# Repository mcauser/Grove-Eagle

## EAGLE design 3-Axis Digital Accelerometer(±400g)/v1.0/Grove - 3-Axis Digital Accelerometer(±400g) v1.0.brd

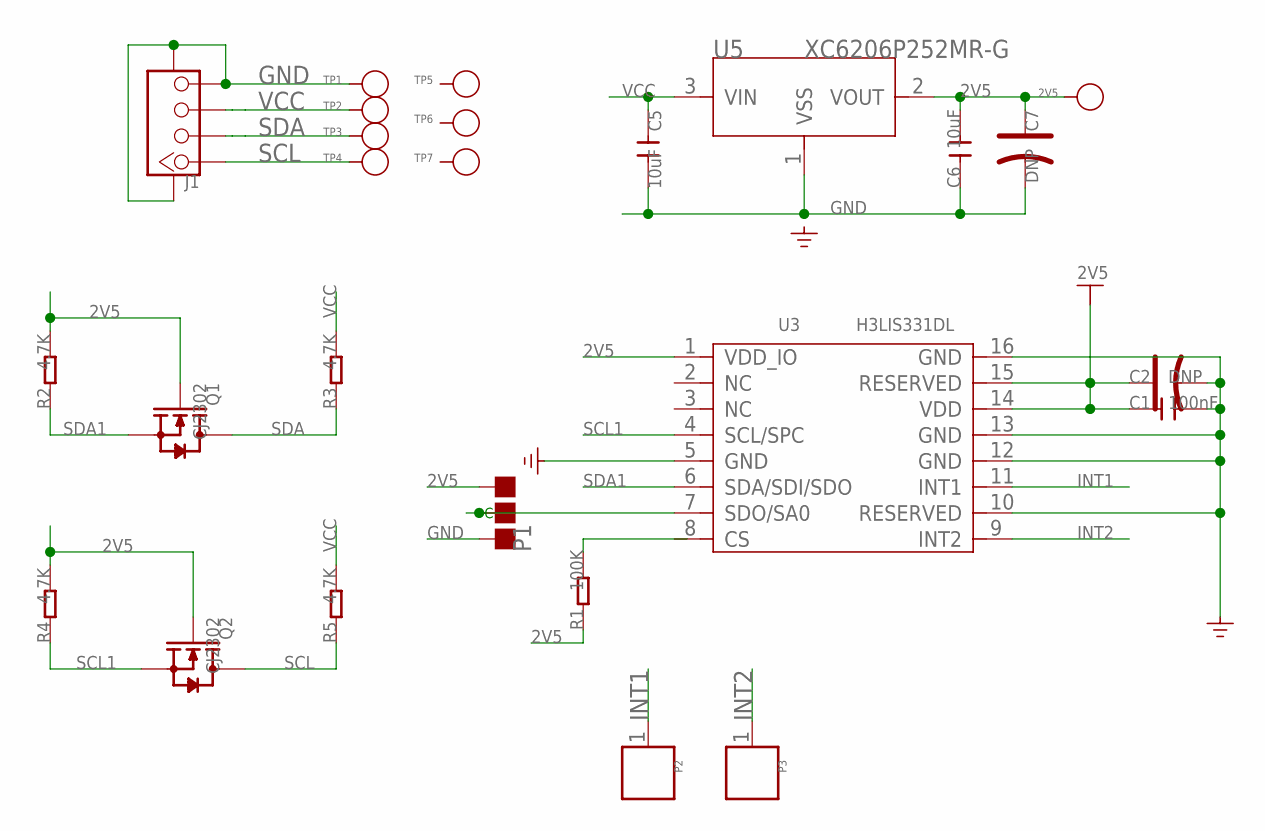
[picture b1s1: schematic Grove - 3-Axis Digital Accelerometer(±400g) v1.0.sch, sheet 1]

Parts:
2V5: PAD-TEST-POINT'4545'; TP_4545
C1: 100nF; C0603
C2, C7: DNP; AVX-A
C5, C6: 10uF; C0805
J1: TWIG-4P-2.0-SMD-FEMALE-REINFORCE'DD'; 4P-SMD-2.0
P1: PAD-JUMPER-3P-40*40; 3P-SMD-4.1X1.5
P2, P3: PAD'60/30'; 1P-65/35MIL
Q1, Q2: CJ2302; SOT23
R1: 100K; R0603
R2, R3, R4, R5: 4.7K; R0603
TP1, TP2, TP3, TP4, TP5, TP6, TP7: PAD-TEST-POINT'4545'; TP_4545
U3: H3LIS331DL; TFLGA-16
U5: XC6206P252MR-G; SOT23

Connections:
2V5: 2V5.T, C1.1, C2.+, C6.2, C7.+, P1.00 (L), Q1.1 (G), Q2.1 (G), R1.1, R2.2, R4.2, U3.1 (VDD_IO), U3.14 (VDD), U3.15 (RESERVED), U5.2 (VOUT)
GND: C1.2, C2.-, C5.2, C6.1, C7.-, J1.4, J1.SS1, J1.SS2, P1.11 (R), TP1.T, U3.5 (GND), U3.10 (RESERVED), U3.12 (GND), U3.13 (GND), U3.16 (GND), U5.1 (VSS)
INT1: P2.1, U3.11 (INT1)
INT2: P3.1, U3.9 (INT2)
unnamed: P1.MM (C), U3.7 (SDO/SA0)
SCL: J1.1, Q2.3 (D), R5.1, TP4.T
SCL1: Q2.2 (S), R4.1, U3.4 (SCL/SPC)
SDA: J1.2, Q1.3 (D), R3.1, TP3.T
SDA1: Q1.2 (S), R2.1, U3.6 (SDA/SDI/SDO)
VCC: C5.1, J1.3, R3.2, R5.2, TP2.T, U5.3 (VIN)

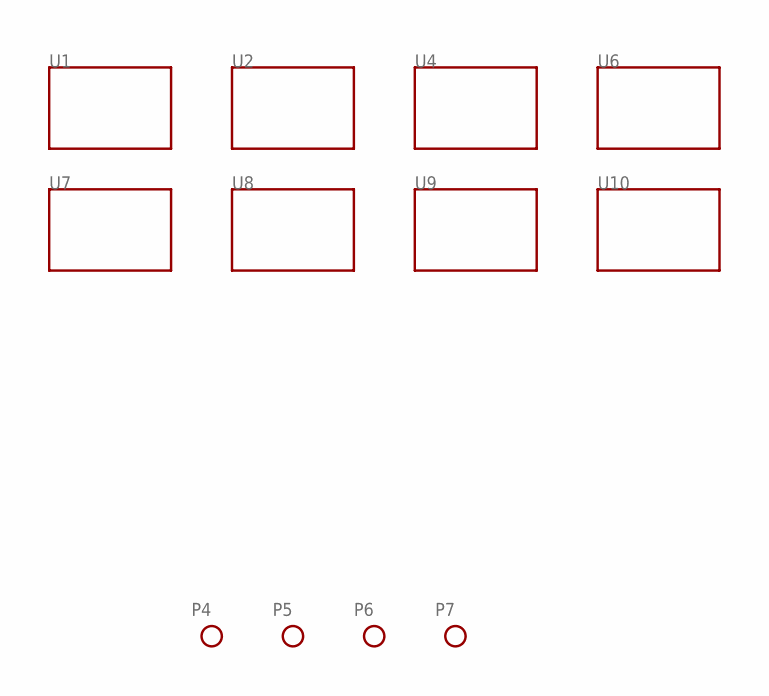
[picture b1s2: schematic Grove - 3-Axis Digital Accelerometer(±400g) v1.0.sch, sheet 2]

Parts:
P4, P5, P6, P7: PAD-MARK; ROUND-MARK-1.0
U1, U2, U4, U6, U7, U8, U9, U10: TWIG'2U'; GROVE-TEST-PLATFORM

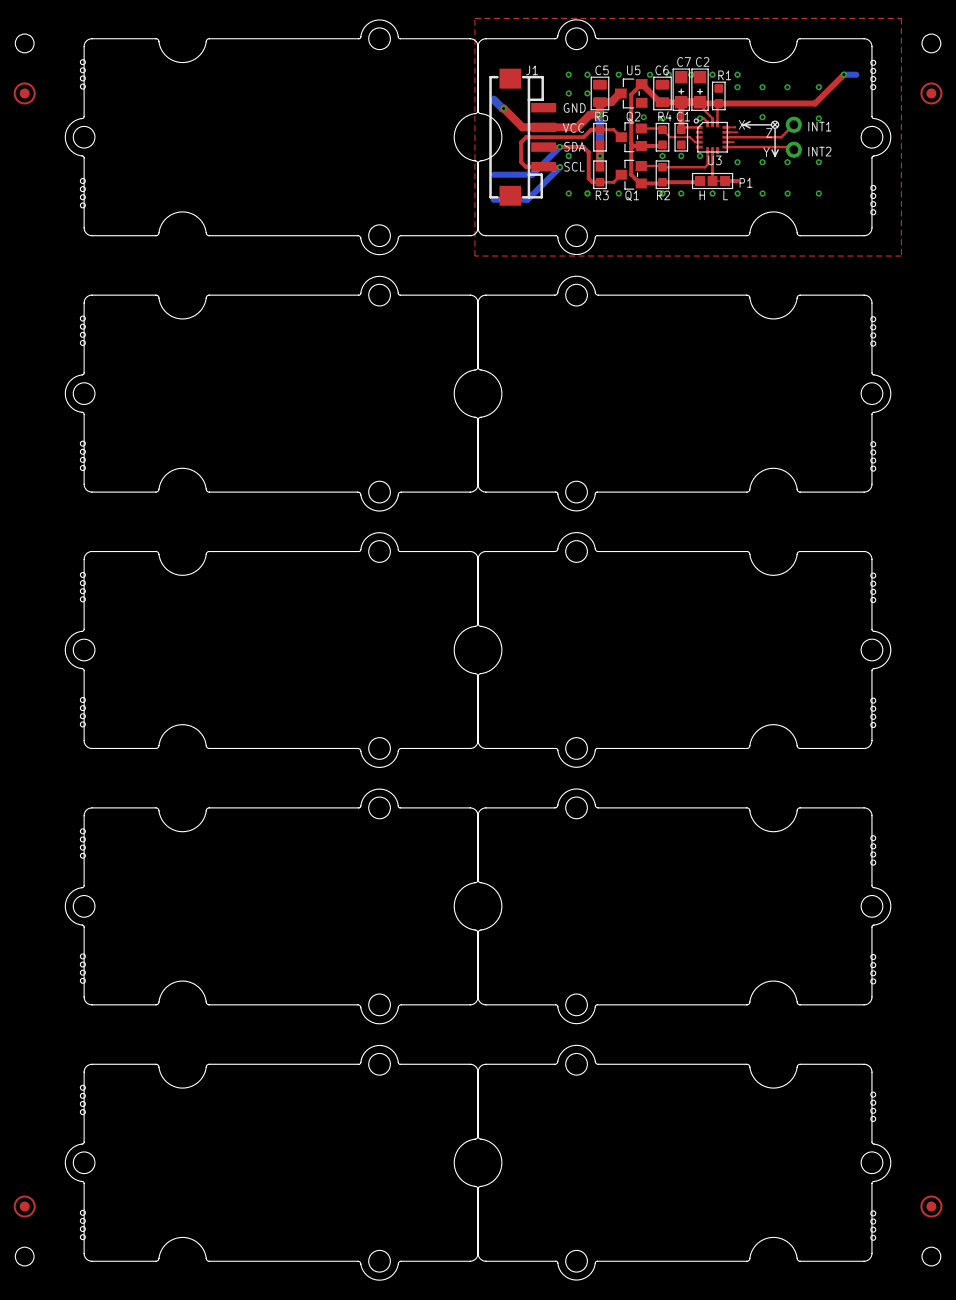
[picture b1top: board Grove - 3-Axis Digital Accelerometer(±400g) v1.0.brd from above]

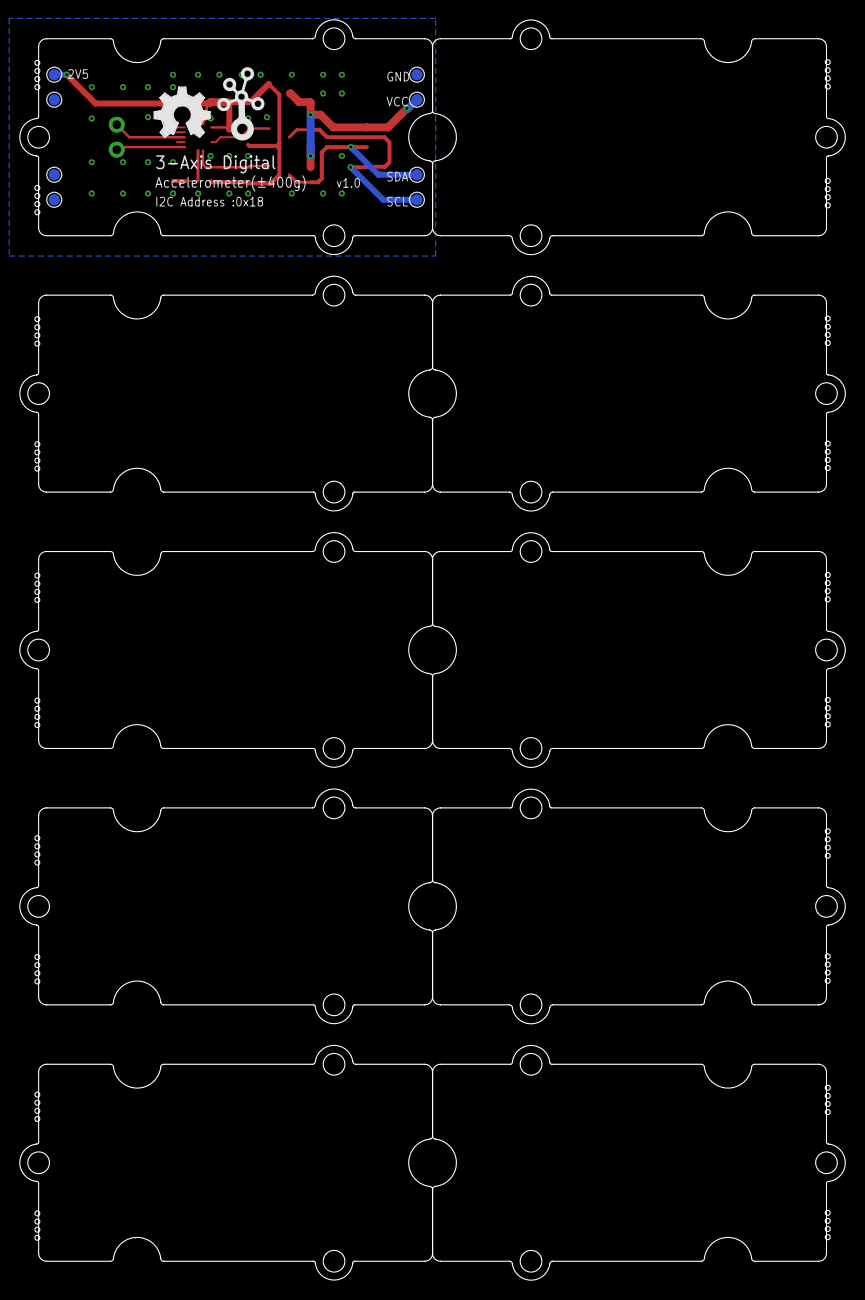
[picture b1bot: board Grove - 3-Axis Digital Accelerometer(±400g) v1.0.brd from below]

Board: 2 copper layers, 83.8 x 128.0 mm, 42 parts (10 on the bottom side), 10 nets.

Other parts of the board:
U11, U12: GROVE-TEST-PLATFORM
U$1: OSHW_FILLX200_NOTEXT
U$3: TWIGLOGO

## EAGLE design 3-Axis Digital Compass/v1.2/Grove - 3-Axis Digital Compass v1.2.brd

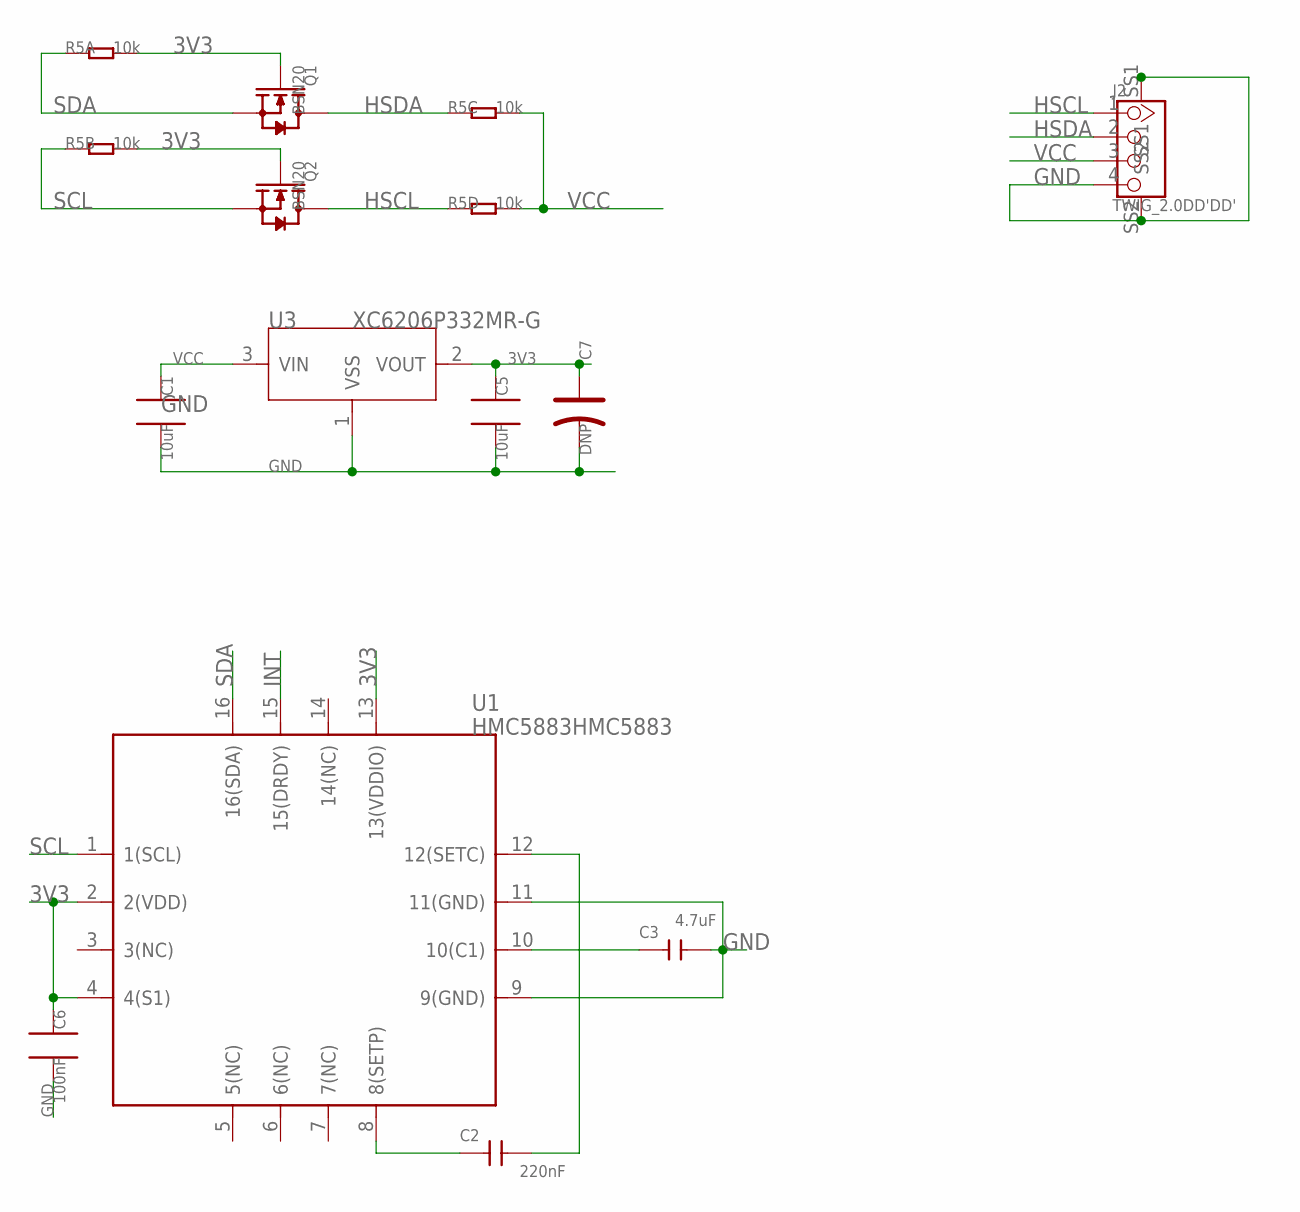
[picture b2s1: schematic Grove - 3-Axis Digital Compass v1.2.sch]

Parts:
C1, C5: 10uF; 0805_S
C2: 220nF; 0603_S
C3: 4.7uF; C0805
C6: 100nF; 0603_S
C7: DNP; AVX-A
J2: TWIG_2.0DD'DD'; 2.0_1X4DD
Q1, Q2: BSN20; SOT23
R5: 10k; R1206-8
U1: HMC5883HMC5883; HMC5883
U3: XC6206P332MR-G; SOT23

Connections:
3V3: C5.1, C6.1, C7.+, Q1.1 (G), Q2.1 (G), R5.7 (2), R5.8 (2), U1.2 (2(VDD)), U1.4 (4(S1)), U1.13 (13(VDDIO)), U3.2 (VOUT)
GND: C1.2, C3.2, C5.2, C6.2, C7.-, J2.4, J2.SS1, J2.SS2, U1.9 (9(GND)), U1.11 (11(GND)), U3.1 (VSS)
HSCL: J2.1, Q2.3 (D), R5.4 (1)
HSDA: J2.2, Q1.3 (D), R5.3 (1)
INT: U1.15 (15(DRDY))
unnamed: C2.1, U1.8 (8(SETP))
unnamed: C2.2, U1.12 (12(SETC))
unnamed: C3.1, U1.10 (10(C1))
SCL: Q2.2 (S), R5.2 (1), U1.1 (1(SCL))
SDA: Q1.2 (S), R5.1, U1.16 (16(SDA))
VCC: C1.1, J2.3, R5.5 (2), R5.6 (2), U3.3 (VIN)

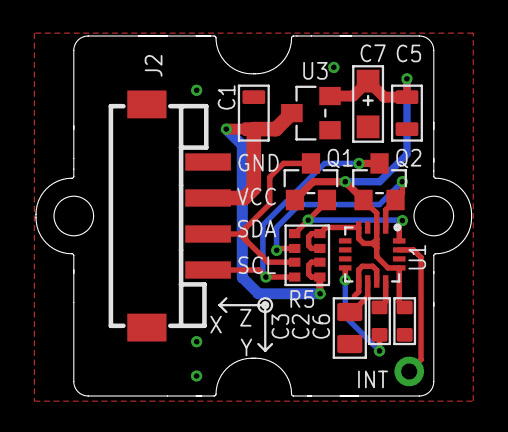
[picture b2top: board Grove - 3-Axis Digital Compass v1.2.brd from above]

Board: 2 copper layers, 24.2 x 20.0 mm, 15 parts (2 on the bottom side), 10 nets.

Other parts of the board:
U$2: 1U-DIM-W/-DRILL
U$4: OSHW_FILLX200_NOTEXT
U$5: TWIGLOGO

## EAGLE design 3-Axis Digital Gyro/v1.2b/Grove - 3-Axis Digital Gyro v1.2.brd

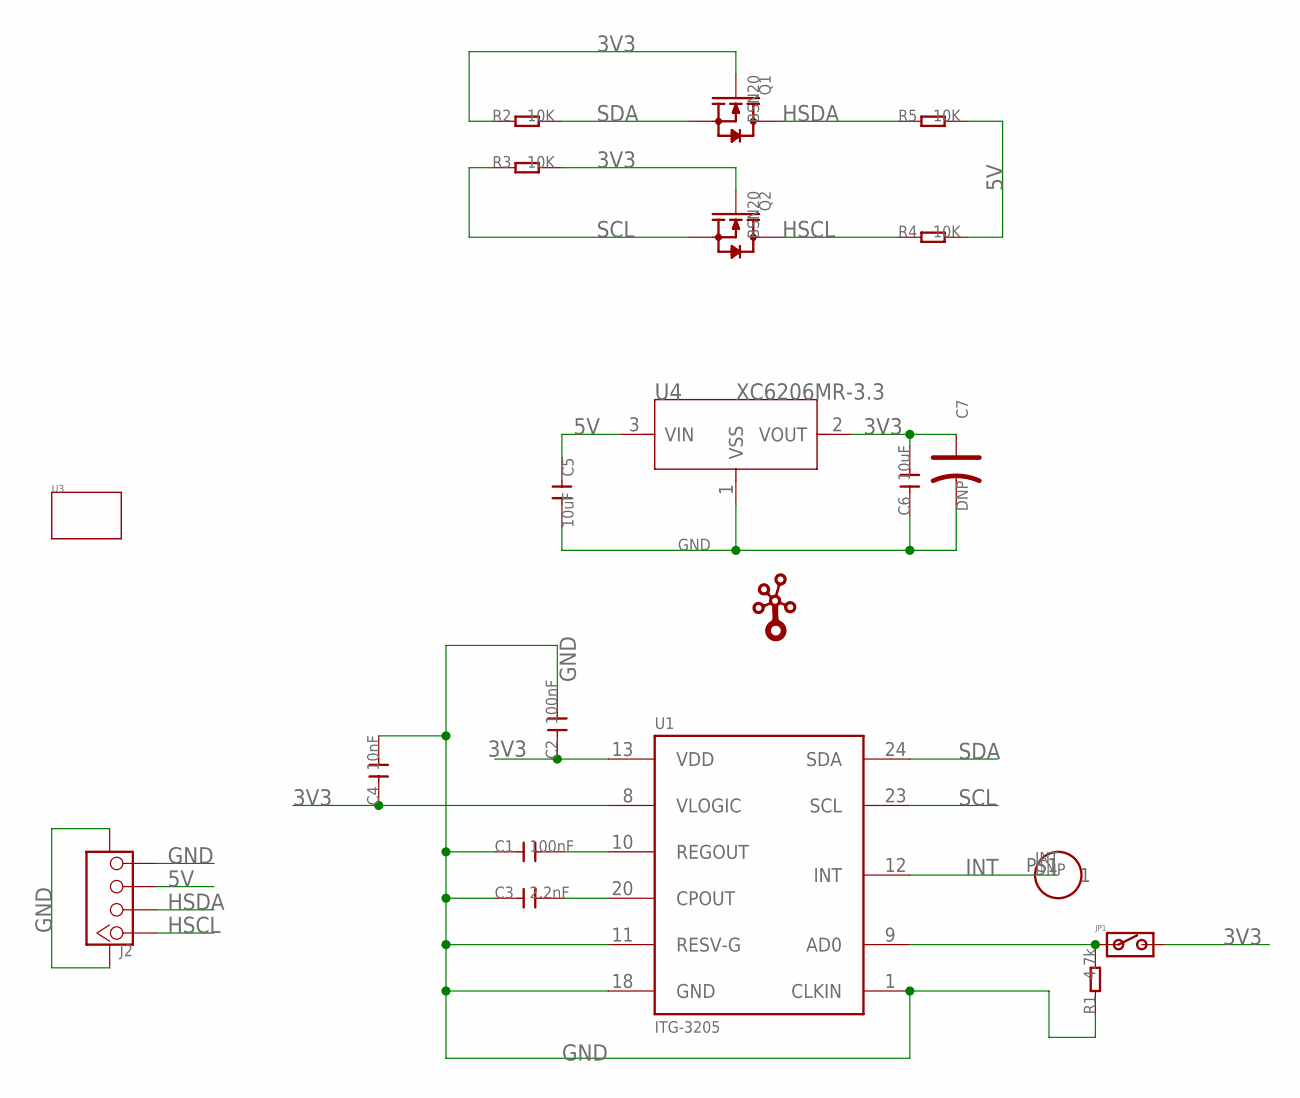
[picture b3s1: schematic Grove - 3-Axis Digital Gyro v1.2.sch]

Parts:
C1, C2: 100nF; C0603
C3: 2.2nF; C0603
C4: 10nF; C0603
C5, C6: 10uF; C0805
C7: DNP; AVX-A
INT: DNP; CK_1X1
J2: TWIG-4P-2.0-SMD-FEMALE-REINFORCE'DD'; 4P-SMD-2.0
JP1: DNP; JP_SW
Q1, Q2: BSN20; SOT23
R1: 4.7k; R0603
R2, R3, R4, R5: 10K; R0603
U1: ITG-3205; QFN-24
U3: TWIG'1U'; 1U-DIM-W/-DRILL
U4: XC6206MR-3.3; SOT23
U$1: TWIGLOGOTWIGLOGO_SMALL; TWIGLOGO_SMALL

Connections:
3V3: C2.1, C4.1, C6.2, C7.+, JP1.2, Q1.1 (G), Q2.1 (G), R2.1, R3.2, U1.8 (VLOGIC), U1.13 (VDD), U4.2 (VOUT)
5V: C5.1, J2.3, R4.2, R5.2, U4.3 (VIN)
GND: C1.1, C2.2, C3.1, C4.2, C5.2, C6.1, C7.-, J2.4, J2.SS1, J2.SS2, R1.1, U1.1 (CLKIN), U1.11 (RESV-G), U1.18 (GND), U4.1 (VSS)
HSCL: J2.1, Q2.3 (D), R4.1
HSDA: J2.2, Q1.3 (D), R5.1
INT: INT.P$1, U1.12 (INT)
unnamed: C3.2, U1.20 (CPOUT)
unnamed: JP1.1, R1.2, U1.9 (AD0)
unnamed: C1.2, U1.10 (REGOUT)
SCL: Q2.2 (S), R3.1, U1.23 (SCL)
SDA: Q1.2 (S), R2.2, U1.24 (SDA)

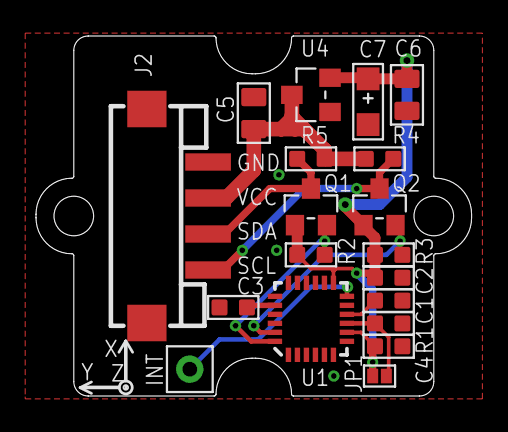
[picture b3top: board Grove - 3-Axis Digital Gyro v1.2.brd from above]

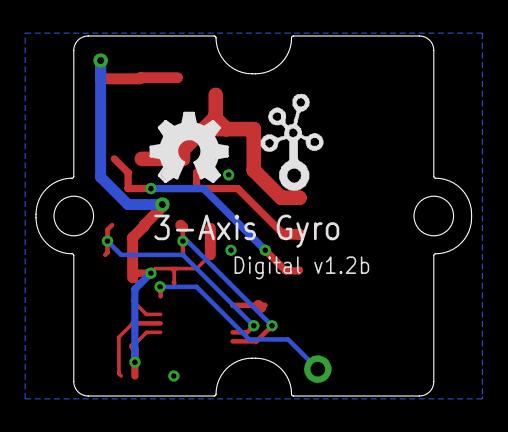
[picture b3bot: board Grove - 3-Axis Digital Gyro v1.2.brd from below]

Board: 2 copper layers, 24.2 x 20.0 mm, 22 parts (2 on the bottom side), 11 nets.

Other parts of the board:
U$2: OSHW_FILLX150_NOTEXT

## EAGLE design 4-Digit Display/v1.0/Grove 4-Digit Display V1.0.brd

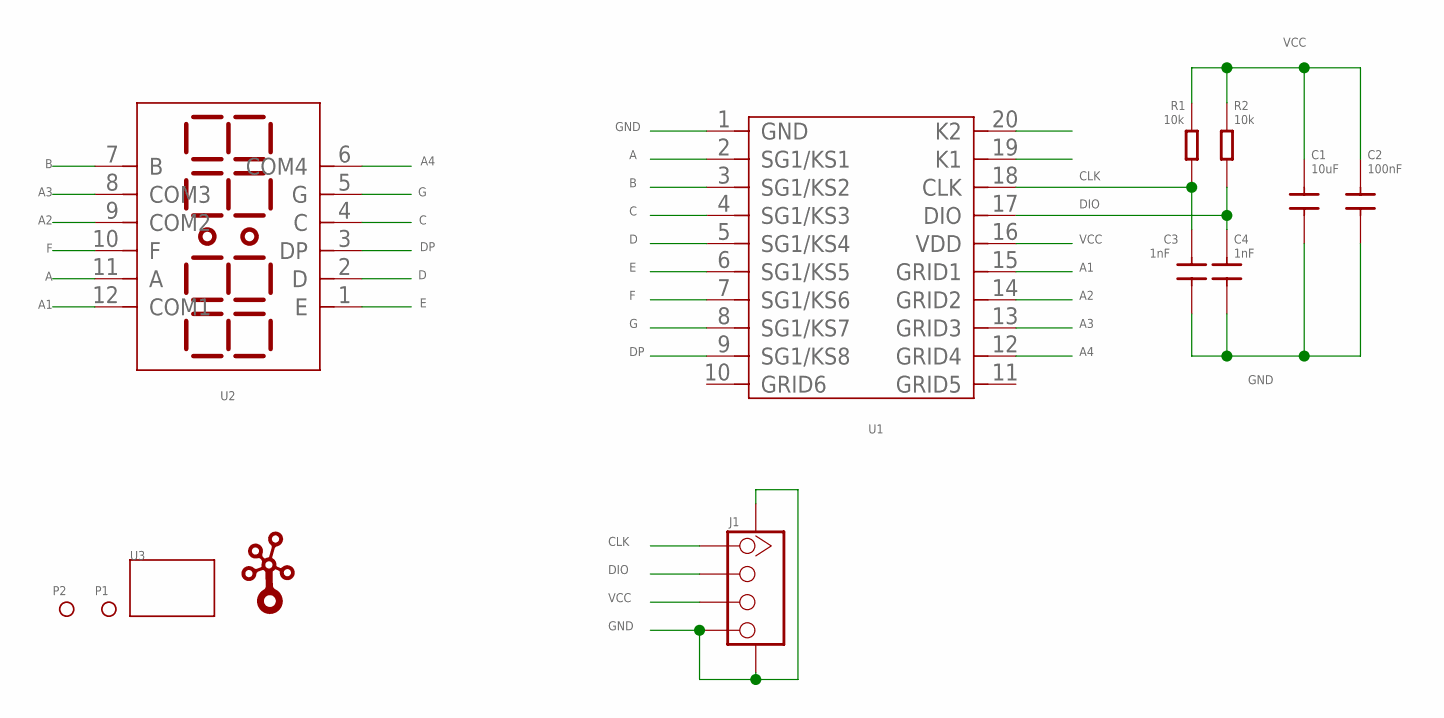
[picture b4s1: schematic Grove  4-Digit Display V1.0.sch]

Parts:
C1: 10uF; 0603
C2: 100nF; 0603
C3, C4: 1nF; 0603
J1: TWIG-4P-2.0-SMD-FEMALE-REINFORCE'90D'; 4P-SMD-2.0-90D
P1, P2: PAD-MARK; ROUND-MARK-0.635
R1, R2: 10k; 0603
U1: TM1637; SOP20-10.45
U2: LED-4-BETY-7-SEG; 7-4-BYTE-SEG-2.54-30X14X7.3H
U3: TWIG-2U; 2U-DIM-W/-DRILL
U$1: LOGO-TWIGTWIGLOGO_SMALL; TWIGLOGO_SMALL

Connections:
A: U1.2 (SG1/KS1), U2.11 (A)
A1: U1.15 (GRID1), U2.12 (COM1)
A2: U1.14 (GRID2), U2.9 (COM2)
A3: U1.13 (GRID3), U2.8 (COM3)
A4: U1.12 (GRID4), U2.6 (COM4)
B: U1.3 (SG1/KS2), U2.7 (B)
C: U1.4 (SG1/KS3), U2.4 (C)
CLK: C3.1, J1.1, R1.2, U1.18 (CLK)
D: U1.5 (SG1/KS4), U2.2 (D)
DIO: C4.1, J1.2, R2.2, U1.17 (DIO)
DP: U1.9 (SG1/KS8), U2.3 (DP)
E: U1.6 (SG1/KS5), U2.1 (E)
F: U1.7 (SG1/KS6), U2.10 (F)
G: U1.8 (SG1/KS7), U2.5 (G)
GND: C1.2, C2.2, C3.2, C4.2, J1.4, J1.SS1, J1.SS2, U1.1 (GND)
VCC: C1.1, C2.1, J1.3, R1.1, R2.1, U1.16 (VDD)

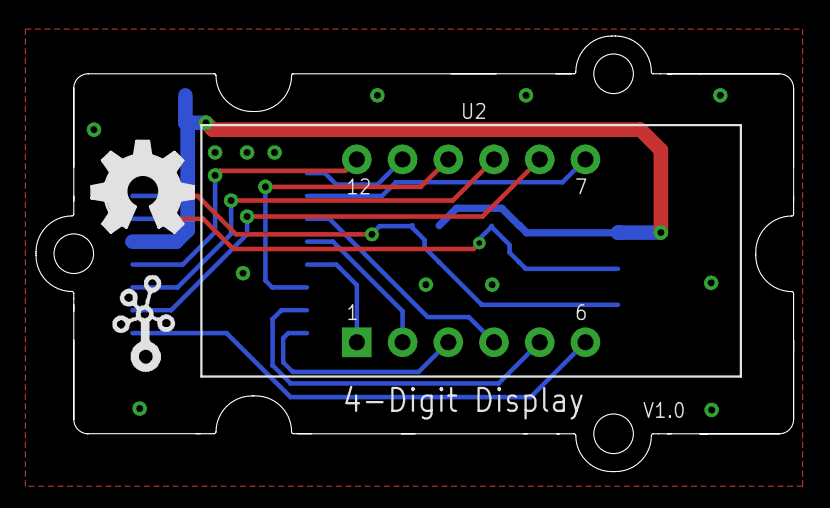
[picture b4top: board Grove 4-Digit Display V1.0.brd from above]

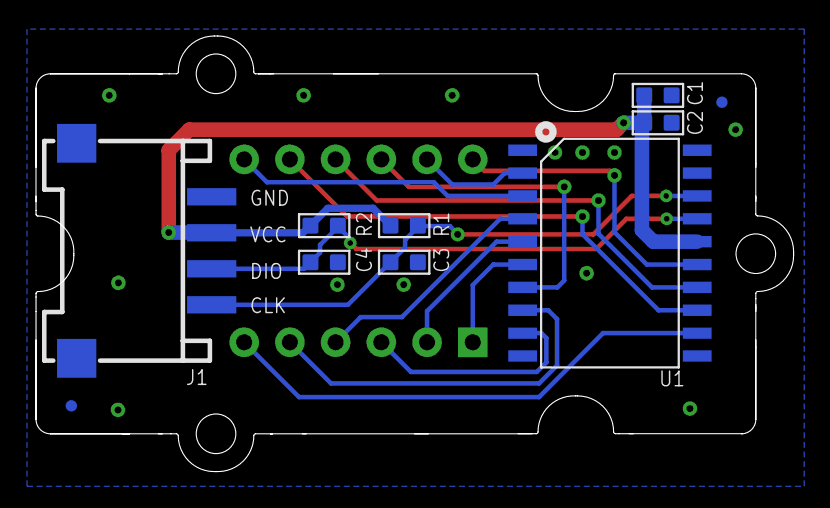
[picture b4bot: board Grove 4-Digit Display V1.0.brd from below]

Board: 2 copper layers, 42.1 x 24.2 mm, 14 parts (10 on the bottom side), 16 nets.

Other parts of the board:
U$12: OSHW_FILLX200_NOTEXT

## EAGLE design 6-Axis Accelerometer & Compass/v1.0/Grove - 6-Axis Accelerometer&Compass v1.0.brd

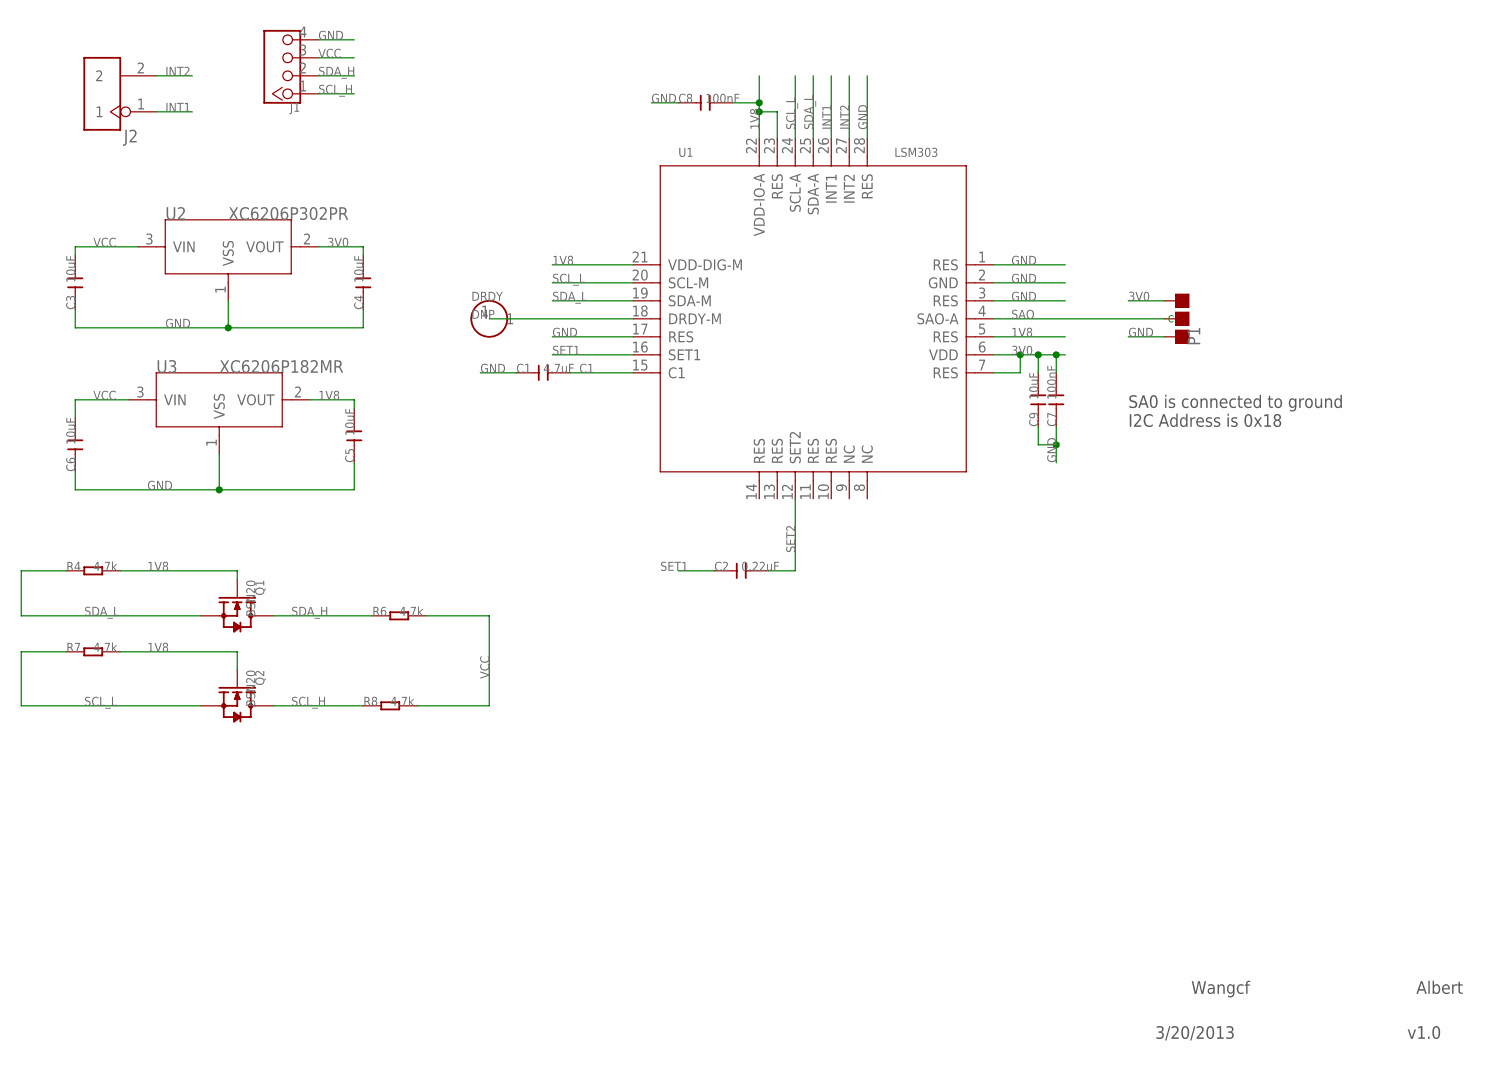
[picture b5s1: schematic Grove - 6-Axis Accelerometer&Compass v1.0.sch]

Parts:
C1: 4.7uF; C0805
C2: 0.22uF; C0603
C3, C4, C5, C6, C9: 10uF; C0805
C7, C8: 100nF; C0603
DRDY: DNP; 1P-65/35MIL
J1: TWIG-4P-2.0-2.0; 4P-2.0
J2: HEADER-2P-65/35MIL; 2P-2.54-65/35MIL
P1: PAD-JUMPER-3P-40*40; 3P-SMD-4.1X1.5
Q1, Q2: BSN20; SOT23
R4, R6, R7, R8: 4.7k; R0603
U1: LSM303; LGA-28
U2: XC6206P302PR; SOT23
U3: XC6206P182MR; SOT23

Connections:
1V8: C5.2, C8.2, Q1.1 (G), Q2.1 (G), R4.2, R7.2, U1.5 (RES), U1.21 (VDD-DIG-M), U1.22 (VDD-IO-A), U1.23 (RES), U3.2 (VOUT)
3V0: C4.2, C7.2, C9.2, P1.00 (L), U1.6 (VDD), U1.7 (RES), U2.2 (VOUT)
C1: C1.2, U1.15 (C1)
DRDY: DRDY.1, U1.18 (DRDY-M)
GND: C1.1, C3.1, C4.1, C5.1, C6.1, C7.1, C8.1, C9.1, J1.4, P1.11 (R), U1.1 (RES), U1.2 (GND), U1.3 (RES), U1.17 (RES), U1.28 (RES), U2.1 (VSS), U3.1 (VSS)
INT1: J2.1, U1.26 (INT1)
INT2: J2.2, U1.27 (INT2)
SAO: P1.MM (C), U1.4 (SAO-A)
SCL_H: J1.1, Q2.3 (D), R8.1
SCL_L: Q2.2 (S), R7.1, U1.20 (SCL-M), U1.24 (SCL-A)
SDA_H: J1.2, Q1.3 (D), R6.1
SDA_L: Q1.2 (S), R4.1, U1.19 (SDA-M), U1.25 (SDA-A)
SET1: C2.1, U1.16 (SET1)
SET2: C2.2, U1.12 (SET2)
VCC: C3.2, C6.2, J1.3, R6.2, R8.2, U2.3 (VIN), U3.3 (VIN)

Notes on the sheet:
SA0 is connected to ground I2C Address is 0x18
Wangcf
3/20/2013
Albert
v1.0

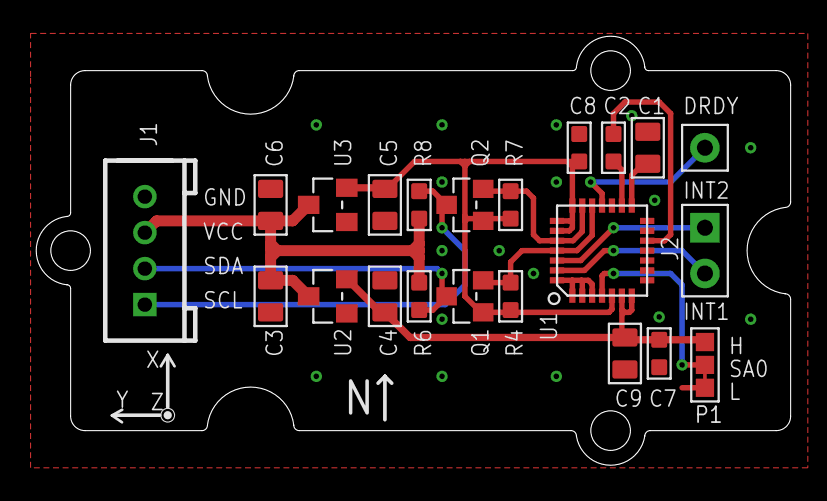
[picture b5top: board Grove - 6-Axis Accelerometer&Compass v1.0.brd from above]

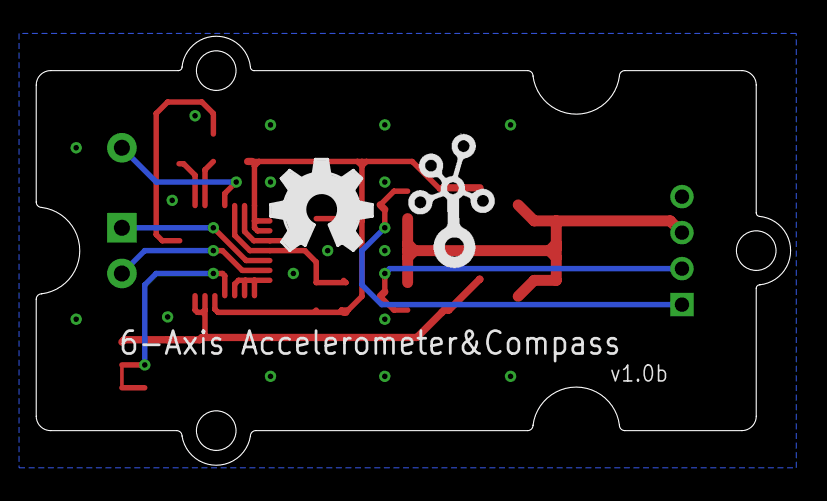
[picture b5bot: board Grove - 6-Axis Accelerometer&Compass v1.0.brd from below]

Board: 2 copper layers, 41.9 x 23.8 mm, 25 parts (2 on the bottom side), 15 nets.

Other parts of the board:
U$2: 2U-DIM-W/DRILL
U$3: TWIGLOGO
U$4: OSHW_FILLX200_NOTEXT

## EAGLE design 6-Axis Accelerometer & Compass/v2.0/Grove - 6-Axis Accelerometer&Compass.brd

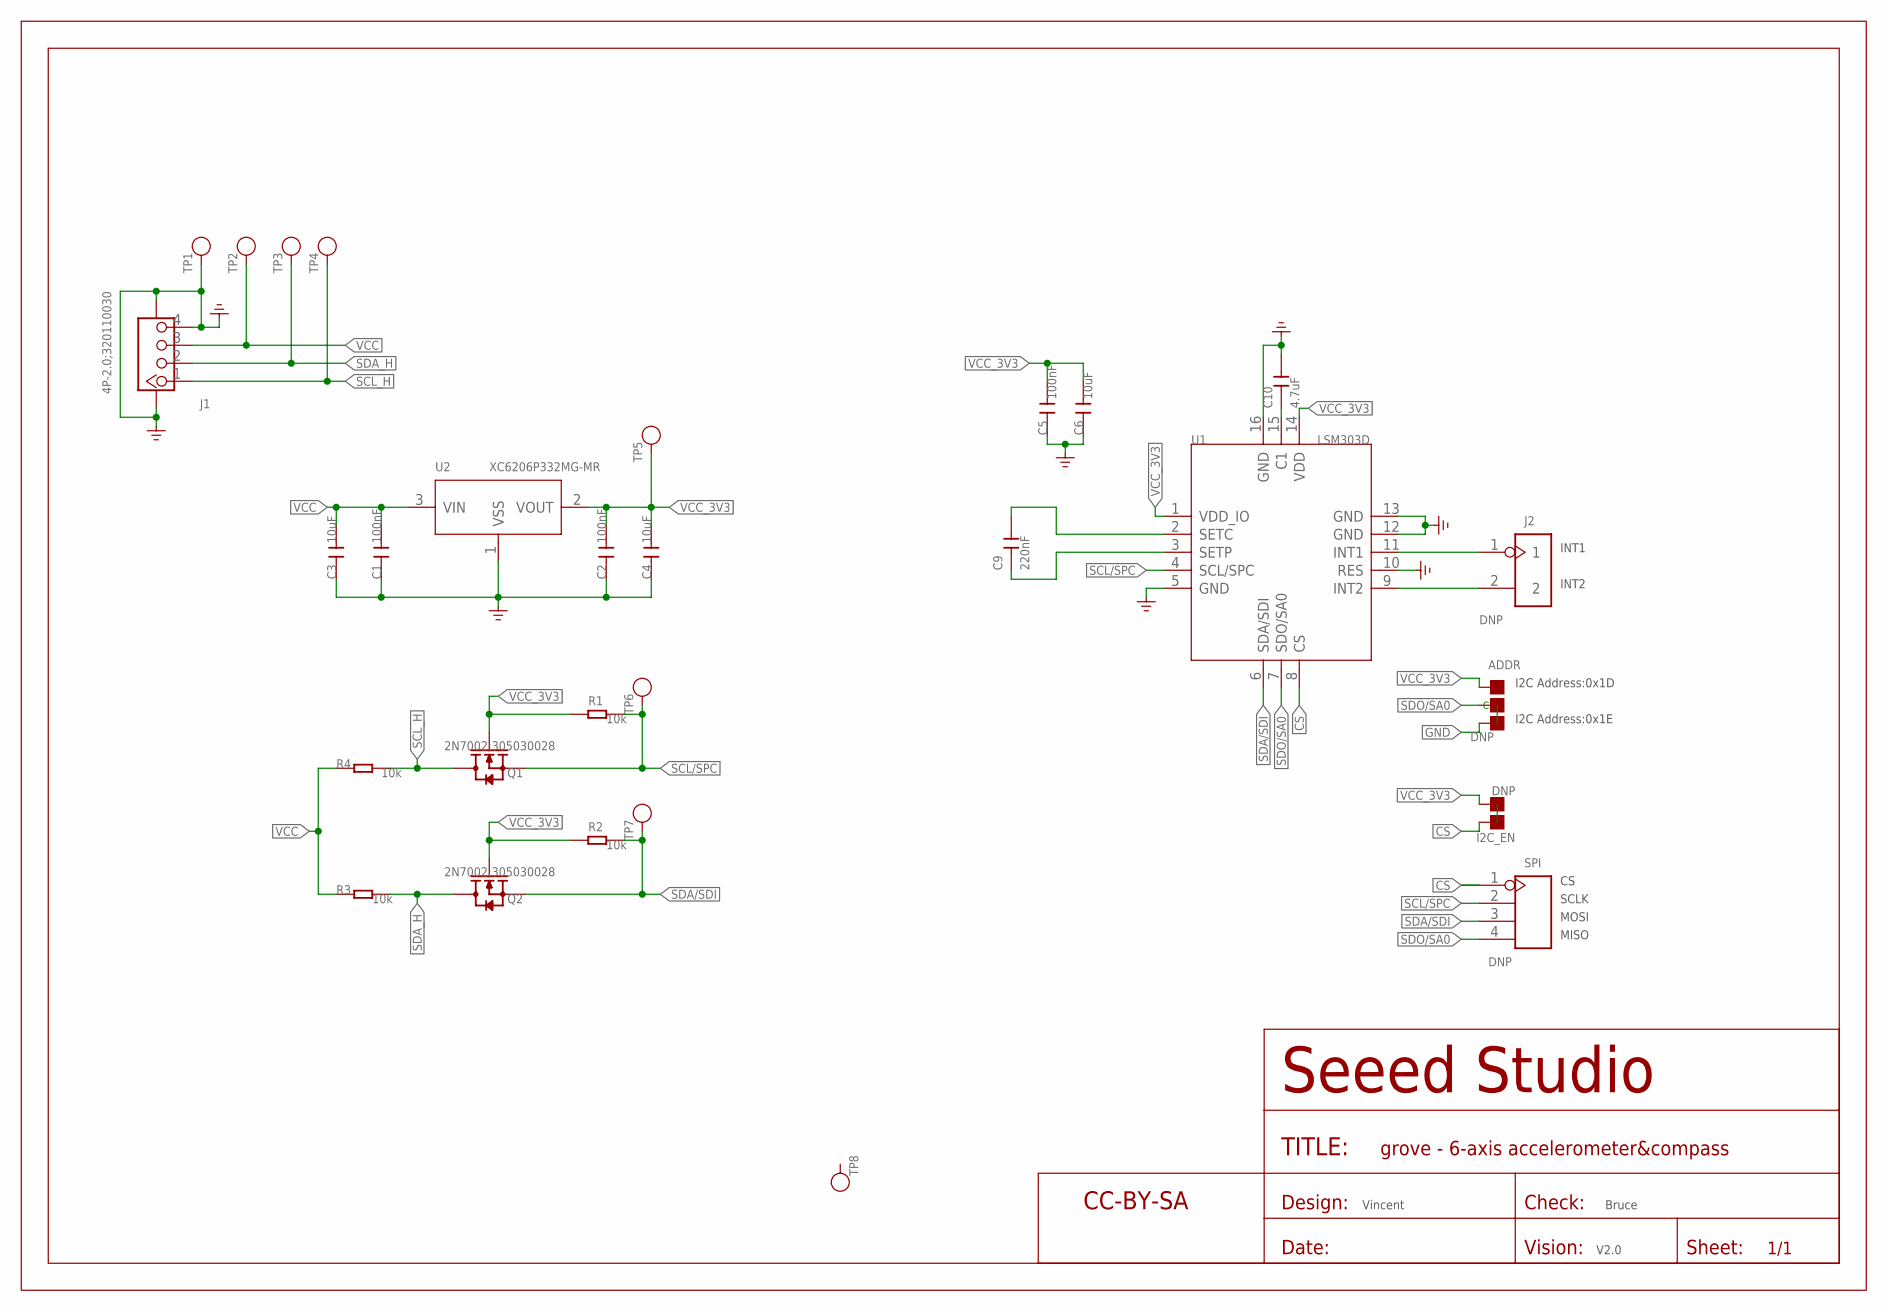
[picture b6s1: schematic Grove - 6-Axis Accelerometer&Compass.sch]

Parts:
ADDR: DNP; 3P-SMD-L4.1*W1.5MM
C1, C2, C5: 100nF; C0603
C3, C4, C6: 10uF; C0805
C9: 220nF; C0603
C10: 4.7uF; C0603
I2C_EN: DNP; 2P-SMD-L1.78*W1.27MM
J1: 4P-2.0;320110030; 4P-SMD-2.0
J2: DNP; 2P-2.54-65/35MIL
Q1, Q2: 2N7002;305030028; SOT-23
R1, R2, R3, R4: 10k; R0603
SPI: DNP; 4P-2.54-65/35MIL
TP1, TP2, TP3, TP4, TP5, TP6, TP7, TP8: DNP; TP-D45MIL
U1: LSM303D; LGA-16
U2: XC6206P332MG-MR; SOT-23
U$1: SEEEDSTUDIO-OPEN-SCH-FRAME; SEEEDSTUDIO-PCB-FRAME

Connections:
CS: I2C_EN.2, SPI.1, U1.8 (CS)
GND: ADDR.11 (R), C1.1, C2.1, C3.1, C4.1, C5.1, C6.1, C10.2, J1.4, J1.SS1, J1.SS2, TP1.T, U1.5 (GND), U1.10 (RES), U1.12 (GND), U1.13 (GND), U1.16 (GND), U2.1 (VSS)
unnamed: C9.2, U1.2 (SETC)
unnamed: C9.1, U1.3 (SETP)
unnamed: C10.1, U1.15 (C1)
unnamed: J2.2, U1.9 (INT2)
unnamed: J2.1, U1.11 (INT1)
SCL/SPC: Q1.2 (S), R1.2, SPI.2, TP6.T, U1.4 (SCL/SPC)
SCL_H: J1.1, Q1.3 (D), R4.2, TP4.T
SDA/SDI: Q2.2 (S), R2.2, SPI.3, TP7.T, U1.6 (SDA/SDI)
SDA_H: J1.2, Q2.3 (D), R3.2, TP3.T
SDO/SA0: ADDR.MM (C), SPI.4, U1.7 (SDO/SA0)
VCC: C1.2, C3.2, J1.3, R3.1, R4.1, TP2.T, U2.3 (VIN)
VCC_3V3: ADDR.00 (L), C2.2, C4.2, C5.2, C6.2, I2C_EN.1, Q1.1 (G), Q2.1 (G), R1.1, R2.1, TP5.T, U1.1 (VDD_IO), U1.14 (VDD), U2.2 (VOUT)

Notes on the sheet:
Vincent
Bruce
V2.0
SCLK
MOSI
MISO
I2C Address:0x1D
I2C Address:0x1E
INT1
INT2

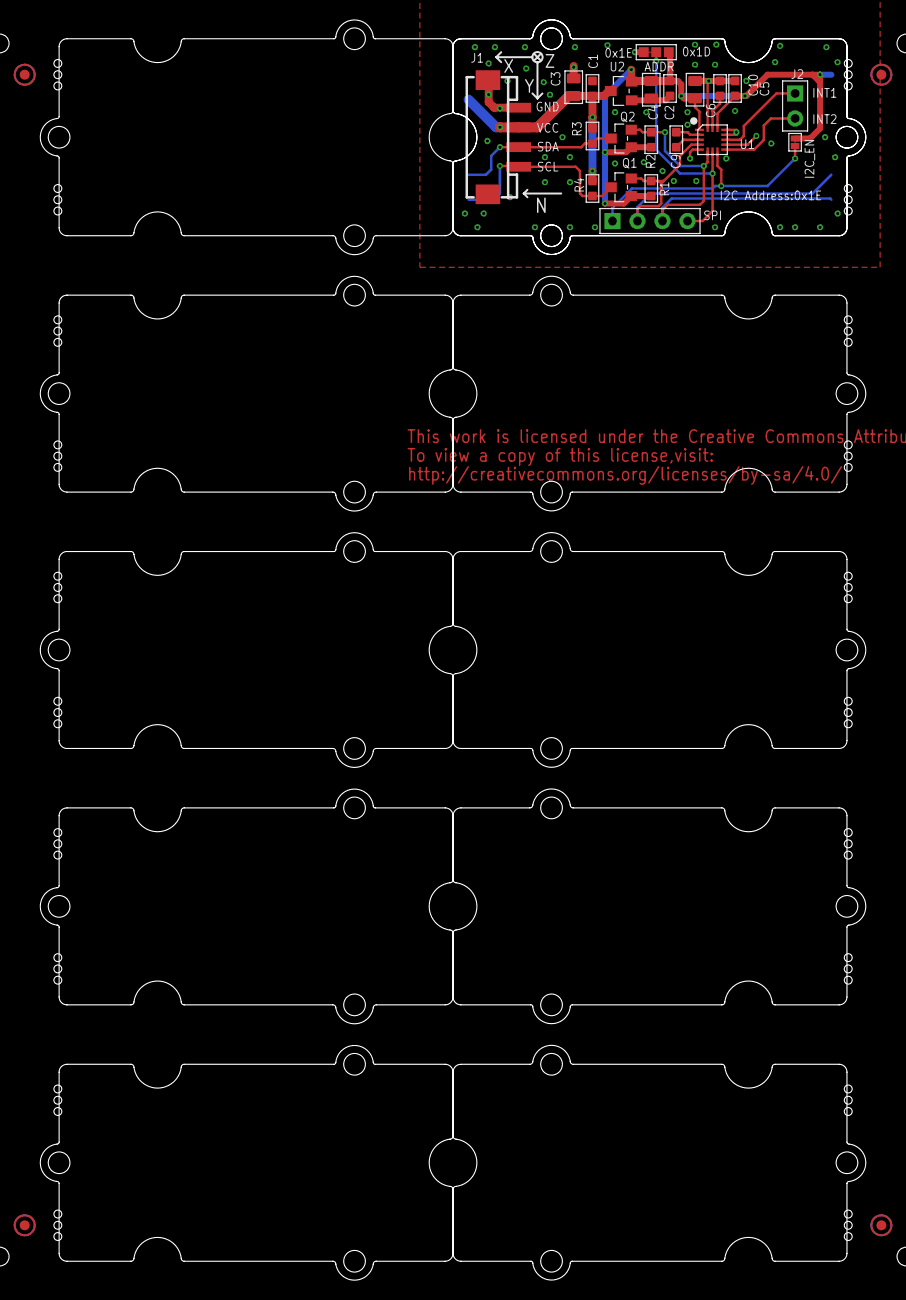
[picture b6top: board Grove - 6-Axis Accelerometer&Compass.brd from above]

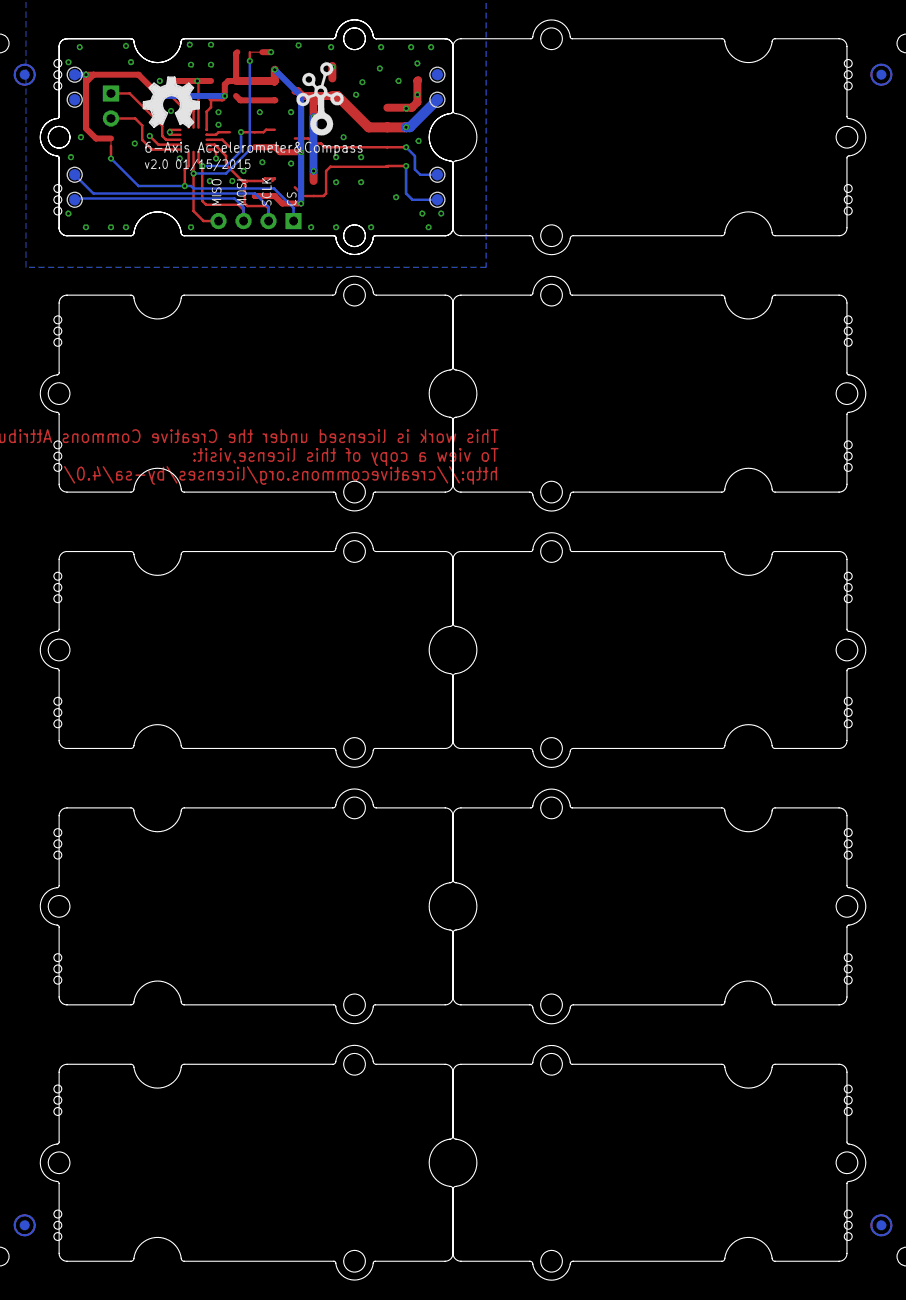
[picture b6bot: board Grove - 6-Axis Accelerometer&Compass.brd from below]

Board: 2 copper layers, 83.8 x 128.0 mm, 51 parts (14 on the bottom side), 14 nets.

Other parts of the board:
P1, P2, P3, P4, P5, P6, P7, P8: ROUND-MARK-1.0
U3, U4, U5, U6, U7, U8, U9, U10, U11, U12: GROVE-TEST-PLATFORM
U$10: GROVE-1*2-TEST-PLATFORM
U$11: GROVE-SILK-BIG
U$12: OSHW_FILLX200_NOTEXT

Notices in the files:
parts and their libraries:
moudle-new: This work is licensed under the Creative Commons Attribution 4.0 International License.
To view a copy of this license,visit:
http://creativecommons.org/licenses/by-sa/4.0
moudle-new: CC-BY-SA
